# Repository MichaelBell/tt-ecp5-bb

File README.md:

# ECP5 breakout board for Tiny Tapeout Carrier

A super minimal breakout, for prototyping Tiny Tapeout designs on an ECP5 FPGA.

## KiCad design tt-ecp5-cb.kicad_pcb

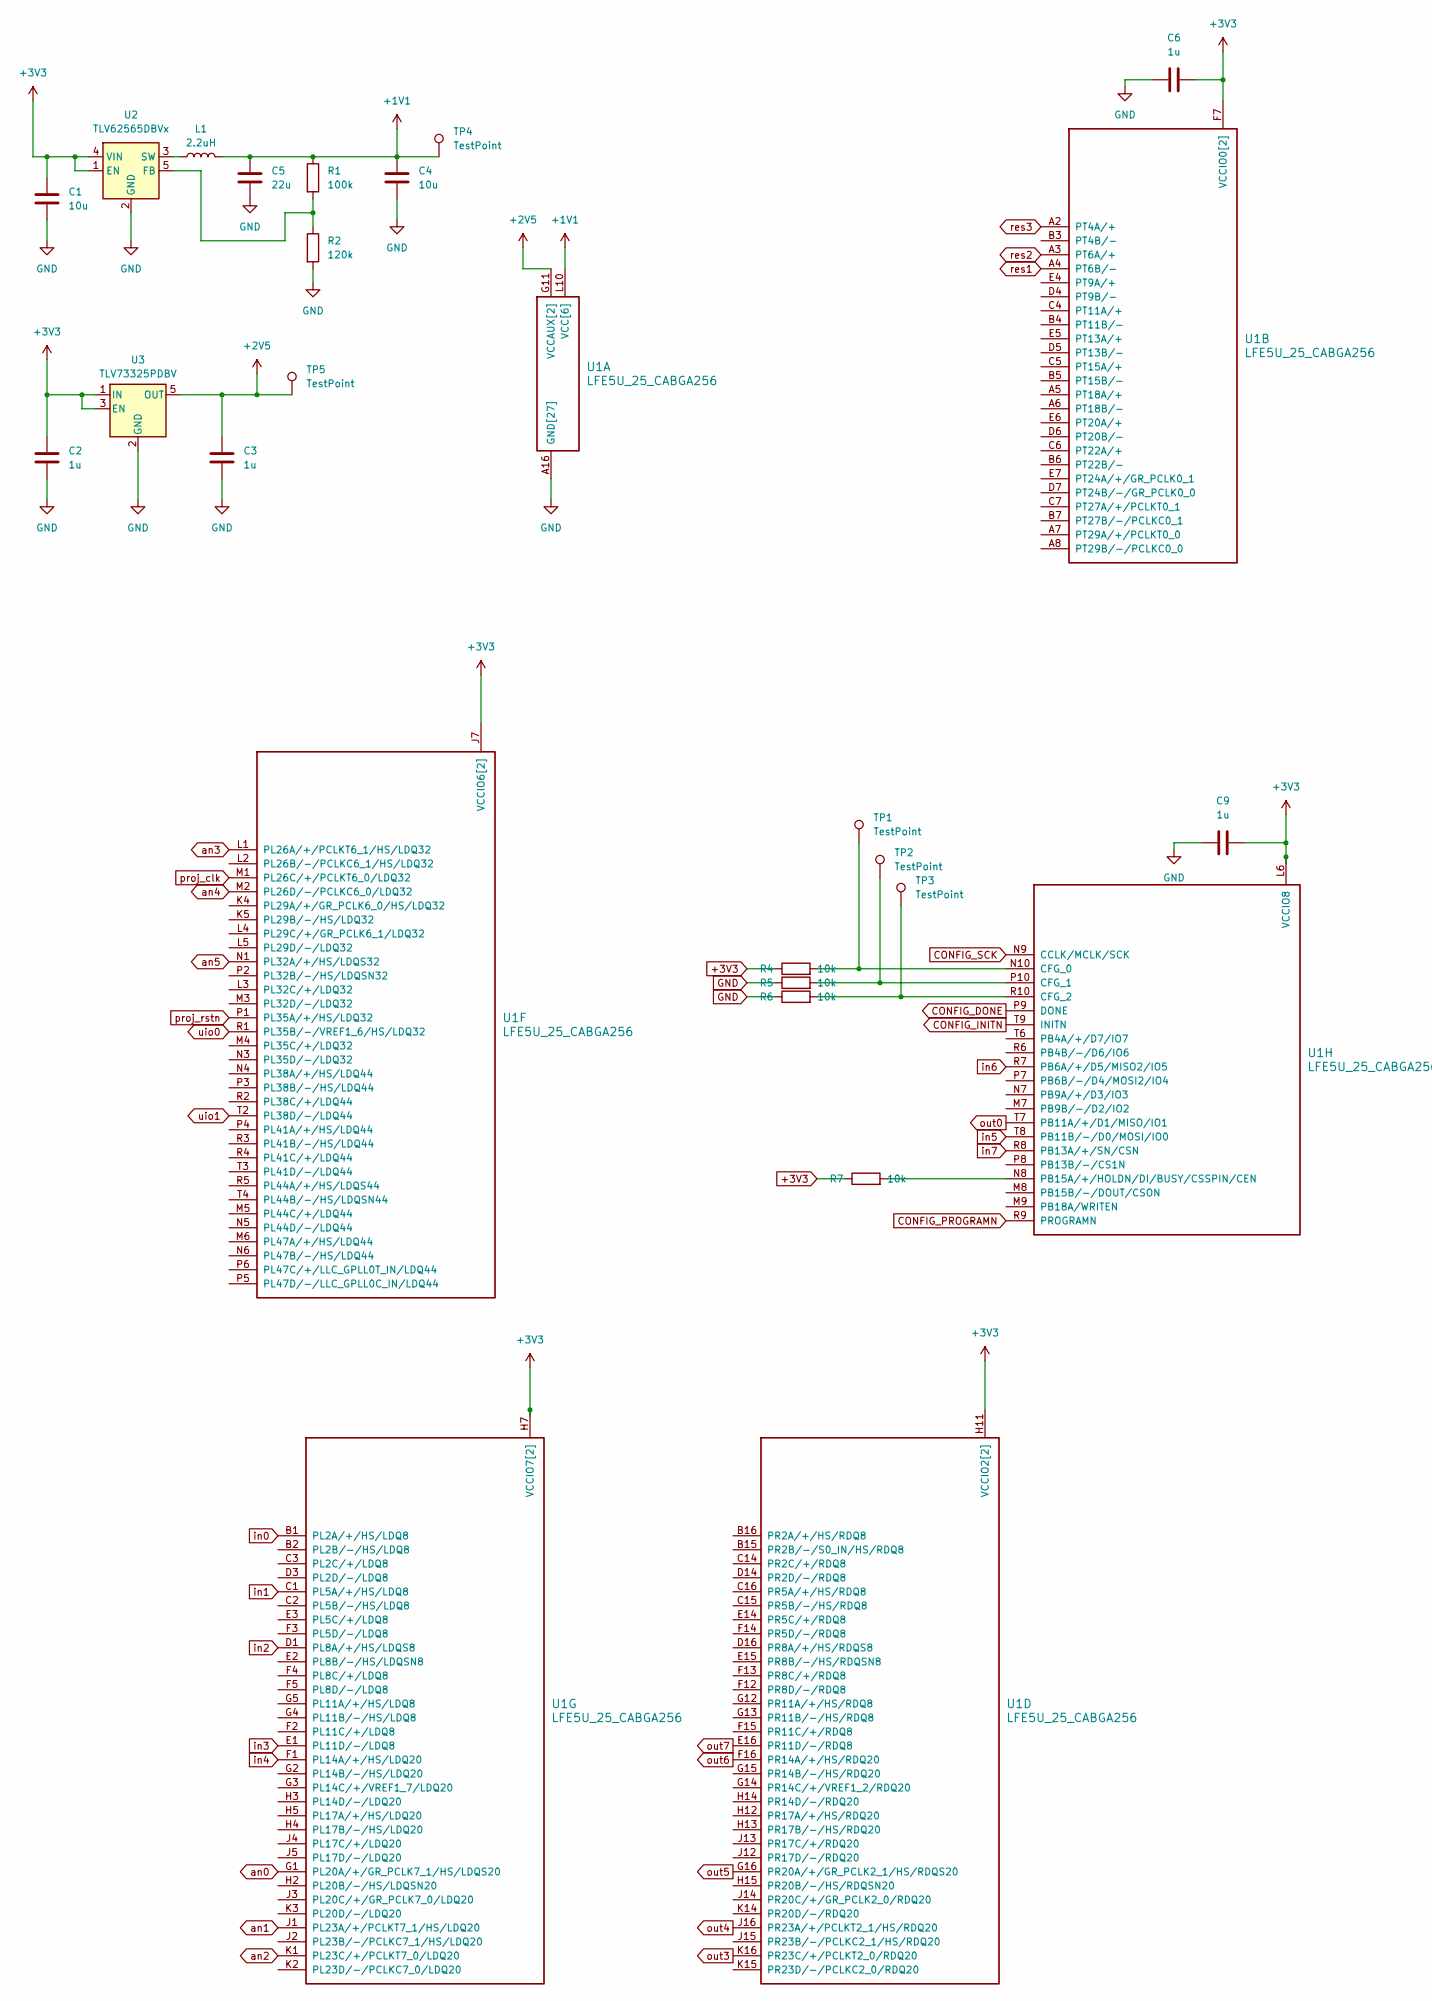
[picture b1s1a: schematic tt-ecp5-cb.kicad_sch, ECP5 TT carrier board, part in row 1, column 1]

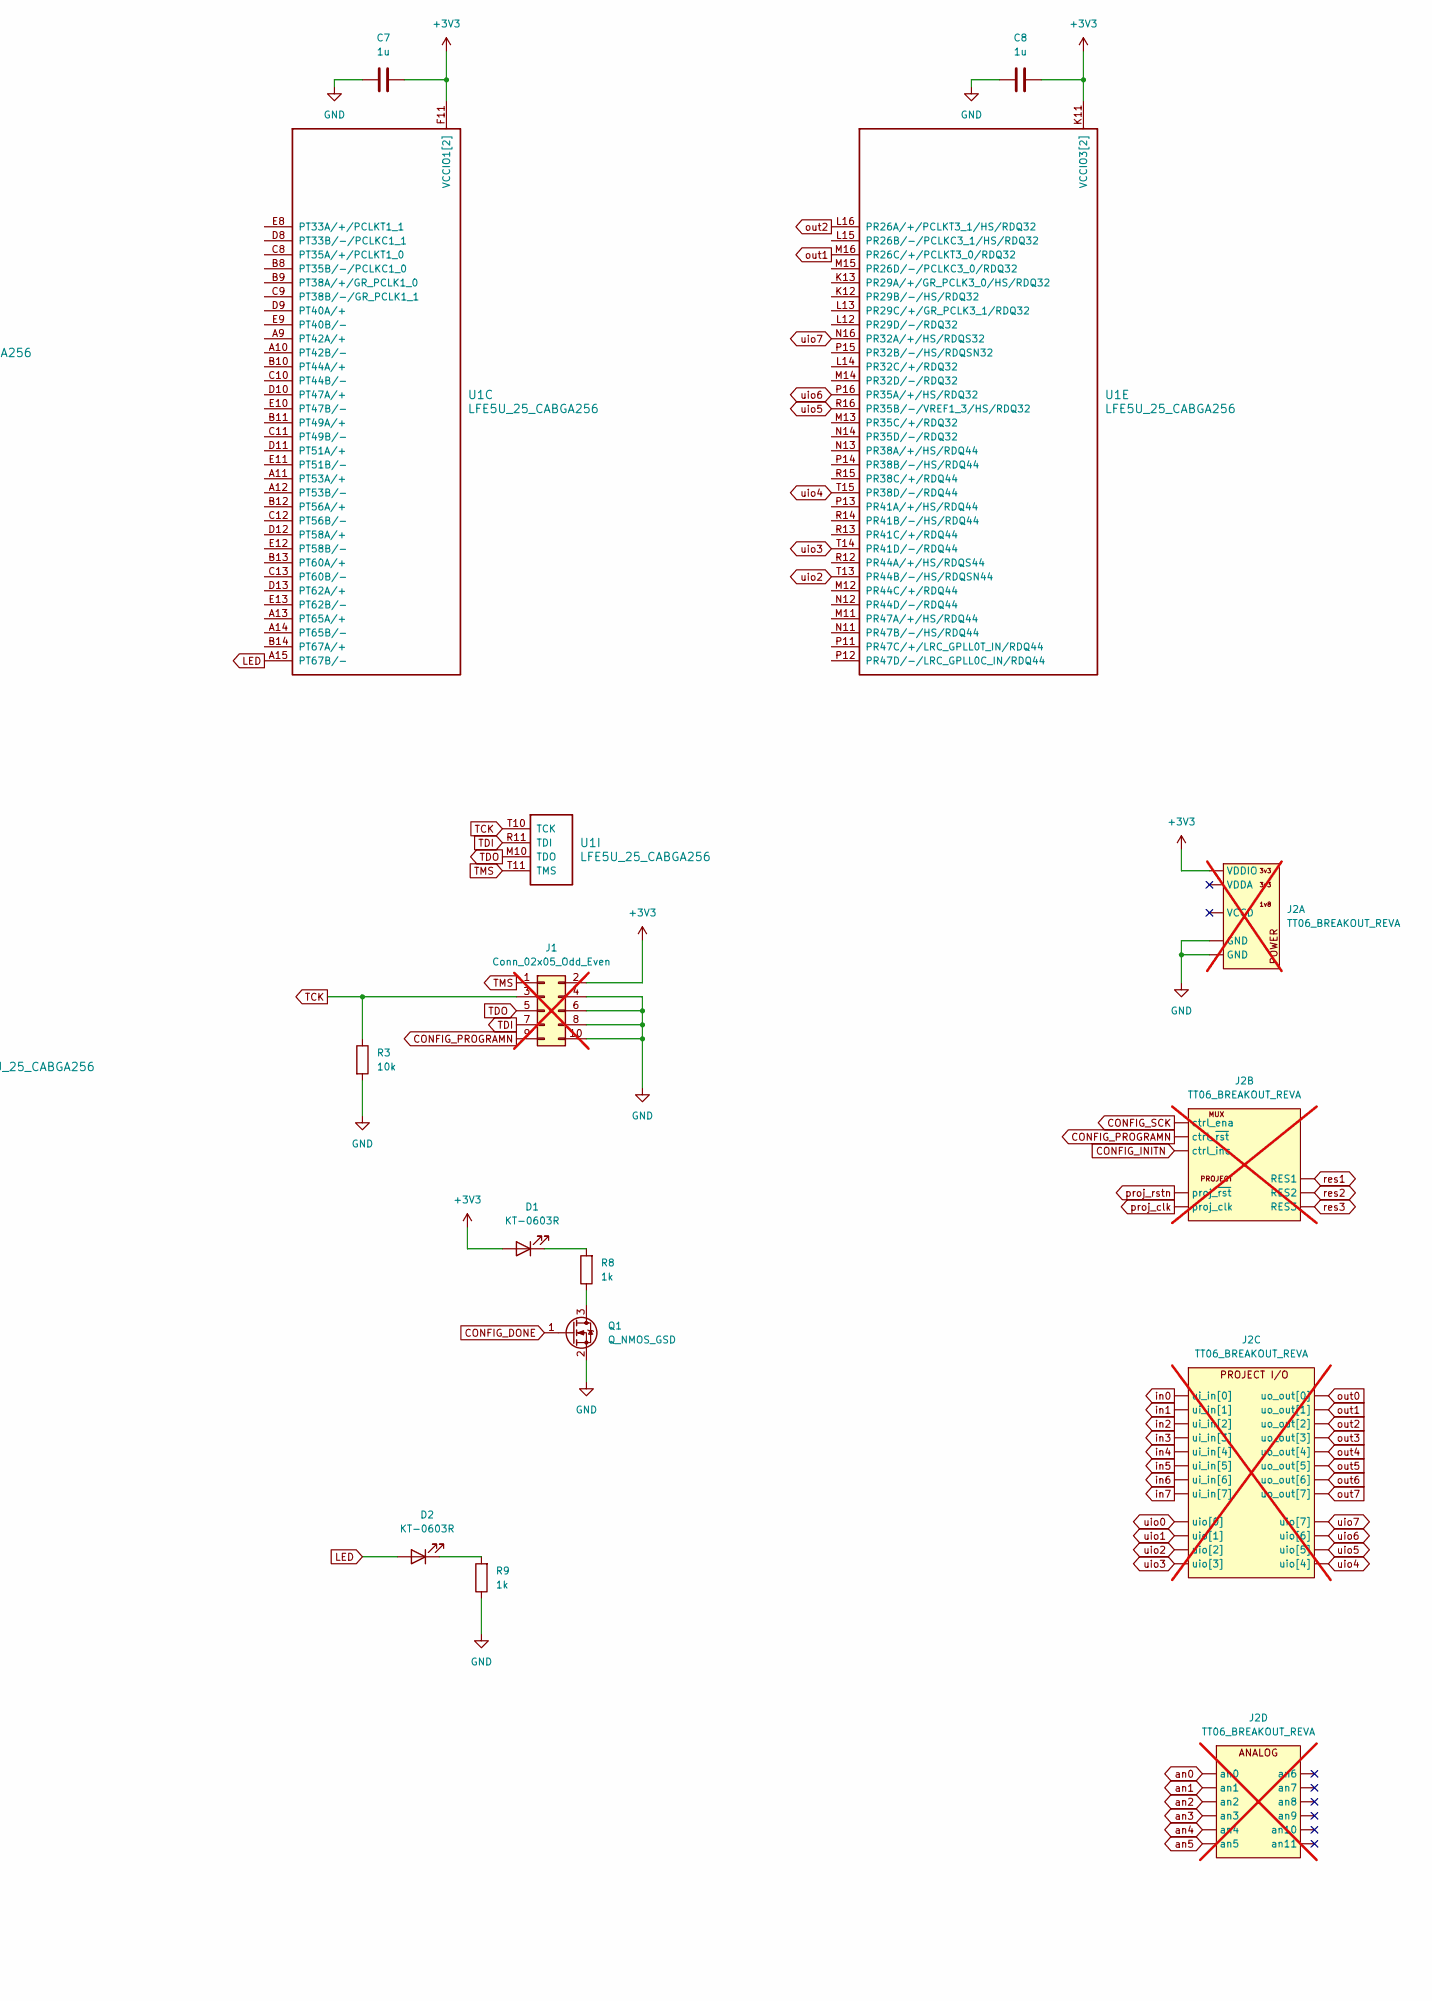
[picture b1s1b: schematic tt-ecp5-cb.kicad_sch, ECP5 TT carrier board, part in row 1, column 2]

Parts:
C1, C4: 10u; C_0402_1005Metric
C2, C3, C6, C7, C8, C9: 1u; C_0402_1005Metric
C5: 22u; C_0603_1608Metric
D1, D2: KT-0603R; LED_0603_1608Metric; JLC C2286
J1: Conn_02x05_Odd_Even; PinHeader_2x05_P2.54mm_Vertical; not fitted
J2: TT06_BREAKOUT_REVA; TT06_CARRIER_ON_DB; not fitted
L1: 2.2uH; L_0805_2012Metric; JLC C281115
Q1: Q_NMOS_GSD; SOT-23; JLC C8545
R1: 100k; R_0402_1005Metric
R2: 120k; R_0603_1608Metric
R3, R4, R5, R6, R7: 10k; R_0603_1608Metric
R8, R9: 1k; R_0402_1005Metric
TP1, TP2, TP3, TP4, TP5: TestPoint; TestPoint_Pad_2.0x2.0mm
U1: LFE5U_25_CABGA256; CABGA-256_L14.0-W14.0-R16-C16-P0.80-TL; JLC C1521614
U2: TLV62565DBVx; SOT-23-5; JLC C87122
U3: TLV73325PDBV; SOT-23-5; JLC C882825

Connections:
+1V1: C4.1, C5.1, L1.2, R1.1, TP4.1, U1.G6 (VCC[6]), U1.G7 (VCC[6]), U1.G9 (VCC[6]), U1.L8 (VCC[6]), U1.L9 (VCC[6]), U1.L10 (VCC[6])
+2V5: C3.1, TP5.1, U1.G11 (VCCAUX[2]), U1.L7 (VCCAUX[2]), U3.5 (OUT)
+3V3: C1.1, C2.1, C6.2, C7.2, C8.2, C9.2, D1.2 (A), J1.2, J2.B4 (VDDIO), R4.1, R7.1, U1.F6 (VCCIO0[2]), U1.F7 (VCCIO0[2]), U1.F10 (VCCIO1[2]), U1.F11 (VCCIO1[2]), U1.H6 (VCCIO7[2]), U1.H7 (VCCIO7[2]), U1.H11 (VCCIO2[2]), U1.J6 (VCCIO6[2]), U1.J7 (VCCIO6[2]), U1.J11 (VCCIO2[2]), U1.K11 (VCCIO3[2]), U1.L6 (VCCIO8), U1.L11 (VCCIO3[2]), U2.1 (EN), U2.4 (VIN), U3.1 (IN), U3.3 (EN)
CONFIG_DONE: Q1.1 (G), U1.P9 (DONE)
CONFIG_INITN: J2.A3 (ctrl_inc), U1.T9 (INITN)
CONFIG_PROGRAMN: J1.9, J2.A4 (ctrl_~rst), U1.R9 (PROGRAMN)
CONFIG_SCK: J2.A2 (ctrl_ena), U1.N9 (CCLK/MCLK/SCK)
GND: C1.2, C2.2, C3.2, C4.2, C5.2, C6.1, C7.1, C8.1, C9.1, J1.4, J1.6, J1.8, J1.10, J2.A1 (GND), J2.A5 (GND), J2.A12 (GND), J2.A15 (GND), J2.A18 (GND), J2.A21 (GND), J2.A23 (GND), J2.A25 (GND), J2.A27 (GND), J2.A29 (GND), J2.A31 (GND), J2.A32 (GND), J2.A33 (GND), J2.A37 (GND), J2.A38 (GND), J2.B1 (GND), J2.B3 (GND), J2.B6 (GND), J2.B8 (GND), J2.B10 (GND), J2.B12 (GND), J2.B14 (GND), J2.B16 (GND), J2.B17 (GND), J2.B18 (GND), J2.B23 (GND), J2.B24 (GND), J2.B29 (GND), J2.B30 (GND), J2.B35 (GND), J2.B36 (GND), J2.B39 (GND), J2.B40 (GND), Q1.2 (S), R2.2, R3.2, R5.1, R6.1, R9.1, U1.A1 (GND[27]), U1.A16 (GND[27]), U1.D2 (GND[27]), U1.D15 (GND[27]), U1.F8 (GND[27]), U1.F9 (GND[27]), U1.G8 (GND[27]), U1.G10 (GND[27]), U1.H1 (GND[27]), U1.H8 (GND[27]), U1.H9 (GND[27]), U1.H10 (GND[27]), U1.H16 (GND[27]), U1.J8 (GND[27]), U1.J9 (GND[27]), U1.J10 (GND[27]), U1.K6 (GND[27]), U1.K7 (GND[27]), U1.K8 (GND[27]), U1.K9 (GND[27]), U1.K10 (GND[27]), U1.N2 (GND[27]), U1.N15 (GND[27]), U1.T1 (GND[27]), U1.T5 (GND[27]), U1.T12 (GND[27]), U1.T16 (GND[27]), U2.2 (GND), U3.2 (GND)
LED: D2.2 (A), U1.A15 (PT67B/-)
unnamed: D1.1 (K), R8.2
unnamed: D2.1 (K), R9.2
unnamed: Q1.3 (D), R8.1
unnamed: R4.2, TP1.1, U1.N10 (CFG_0)
unnamed: R5.2, TP2.1, U1.P10 (CFG_1)
unnamed: R6.2, TP3.1, U1.R10 (CFG_2)
unnamed: R7.2, U1.N8 (PB15A/+/HOLDN/DI/BUSY/CSSPIN/CEN)
unnamed: R1.2, R2.1, U2.5 (FB)
unnamed: L1.1, U2.3 (SW)
TCK: J1.3, R3.1, U1.T10 (TCK)
TDI: J1.7, U1.R11 (TDI)
TDO: J1.5, U1.M10 (TDO)
TMS: J1.1, U1.T11 (TMS)
an0: J2.A20 (an0), U1.G1 (PL20A/+/GR_PCLK7_1/HS/LDQS20)
an1: J2.A22 (an1), U1.J1 (PL23A/+/PCLKT7_1/HS/LDQ20)
an2: J2.A24 (an2), U1.K1 (PL23C/+/PCLKT7_0/LDQ20)
an3: J2.A26 (an3), U1.L1 (PL26A/+/PCLKT6_1/HS/LDQ32)
an4: J2.A28 (an4), U1.M2 (PL26D/-/PCLKC6_0/LDQ32)
an5: J2.A30 (an5), U1.N1 (PL32A/+/HS/LDQS32)
in0: J2.A9 (ui_in[0]), U1.B1 (PL2A/+/HS/LDQ8)
in1: J2.A11 (ui_in[1]), U1.C1 (PL5A/+/HS/LDQ8)
in2: J2.A14 (ui_in[2]), U1.D1 (PL8A/+/HS/LDQS8)
in3: J2.A13 (ui_in[3]), U1.E1 (PL11D/-/LDQ8)
in4: J2.A17 (ui_in[4]), U1.F1 (PL14A/+/HS/LDQ20)
in5: J2.A19 (ui_in[5]), U1.T8 (PB11B/-/D0/MOSI/IO0)
in6: J2.A16 (ui_in[6]), U1.R7 (PB6A/+/D5/MISO2/IO5)
in7: J2.A34 (ui_in[7]), U1.R8 (PB13A/+/SN/CSN)
out0: J2.B27 (uo_out[0]), U1.T7 (PB11A/+/D1/MISO/IO1)
out1: J2.B28 (uo_out[1]), U1.M16 (PR26C/+/PCLKT3_0/RDQ32)
out2: J2.B25 (uo_out[2]), U1.L16 (PR26A/+/PCLKT3_1/HS/RDQ32)
out3: J2.B26 (uo_out[3]), U1.K16 (PR23C/+/PCLKT2_0/RDQ20)
out4: J2.B21 (uo_out[4]), U1.J16 (PR23A/+/PCLKT2_1/HS/RDQ20)
out5: J2.B22 (uo_out[5]), U1.G16 (PR20A/+/GR_PCLK2_1/HS/RDQS20)
out6: J2.B19 (uo_out[6]), U1.F16 (PR14A/+/HS/RDQ20)
out7: J2.B20 (uo_out[7]), U1.E16 (PR11D/-/RDQ8)
proj_clk: J2.A35 (proj_clk), U1.M1 (PL26C/+/PCLKT6_0/LDQ32)
proj_rstn: J2.A36 (proj_~rst), U1.P1 (PL35A/+/HS/LDQ32)
res1: J2.A6 (RES1), U1.A4 (PT6B/-)
res2: J2.A8 (RES2), U1.A3 (PT6A/+)
res3: J2.A10 (RES3), U1.A2 (PT4A/+)
uio0: J2.A39 (uio[0]), U1.R1 (PL35B/-/VREF1_6/HS/LDQ32)
uio1: J2.A40 (uio[1]), U1.T2 (PL38D/-/LDQ44)
uio2: J2.B37 (uio[2]), U1.T13 (PR44B/-/HS/RDQSN44)
uio3: J2.B38 (uio[3]), U1.T14 (PR41D/-/RDQ44)
uio4: J2.B33 (uio[4]), U1.T15 (PR38D/-/RDQ44)
uio5: J2.B34 (uio[5]), U1.R16 (PR35B/-/VREF1_3/HS/RDQ32)
uio6: J2.B31 (uio[6]), U1.P16 (PR35A/+/HS/RDQ32)
uio7: J2.B32 (uio[7]), U1.N16 (PR32A/+/HS/RDQS32)

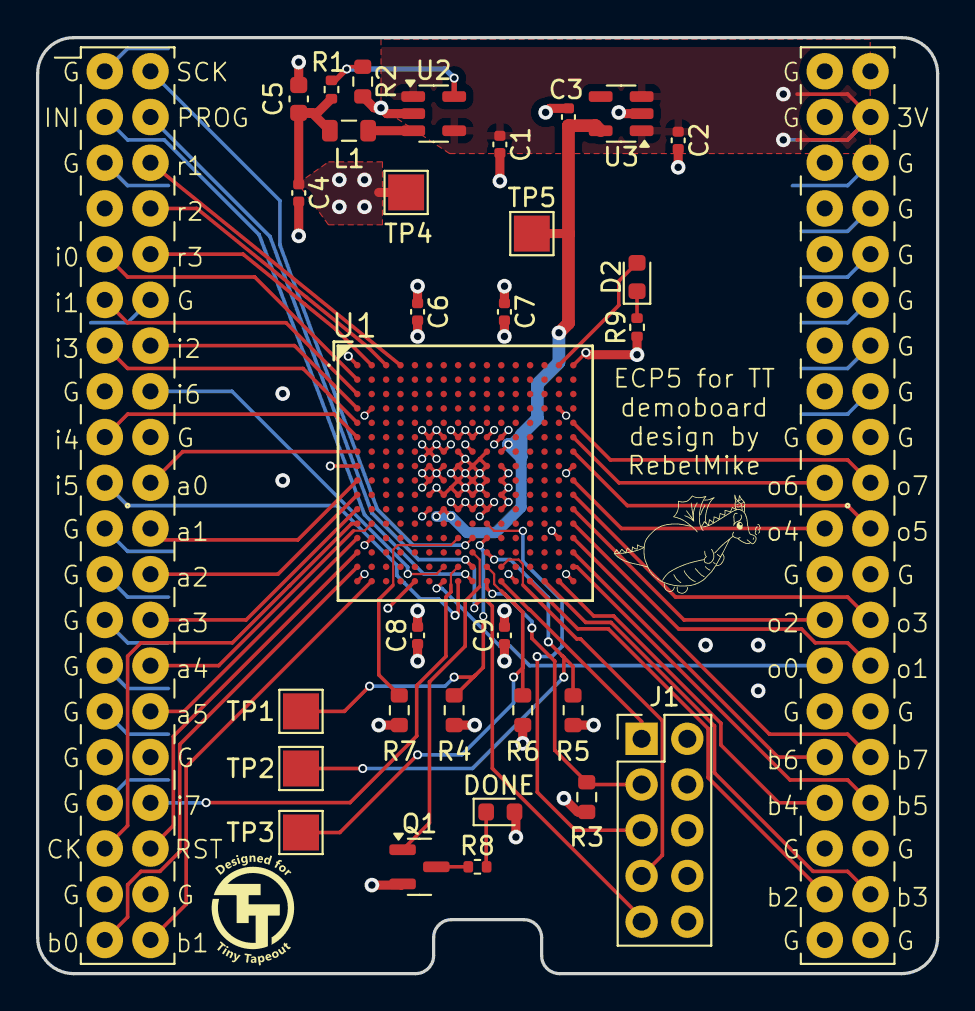
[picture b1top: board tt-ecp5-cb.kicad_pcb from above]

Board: 4 copper layers, 50.0 x 52.0 mm, 32 parts (0 on the bottom side), 57 nets.

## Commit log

2025-02-20 Tweaks
2025-03-08 Silkscreen, test pads
2025-03-09 First version
2025-03-21 ECP programming from TT demo board
